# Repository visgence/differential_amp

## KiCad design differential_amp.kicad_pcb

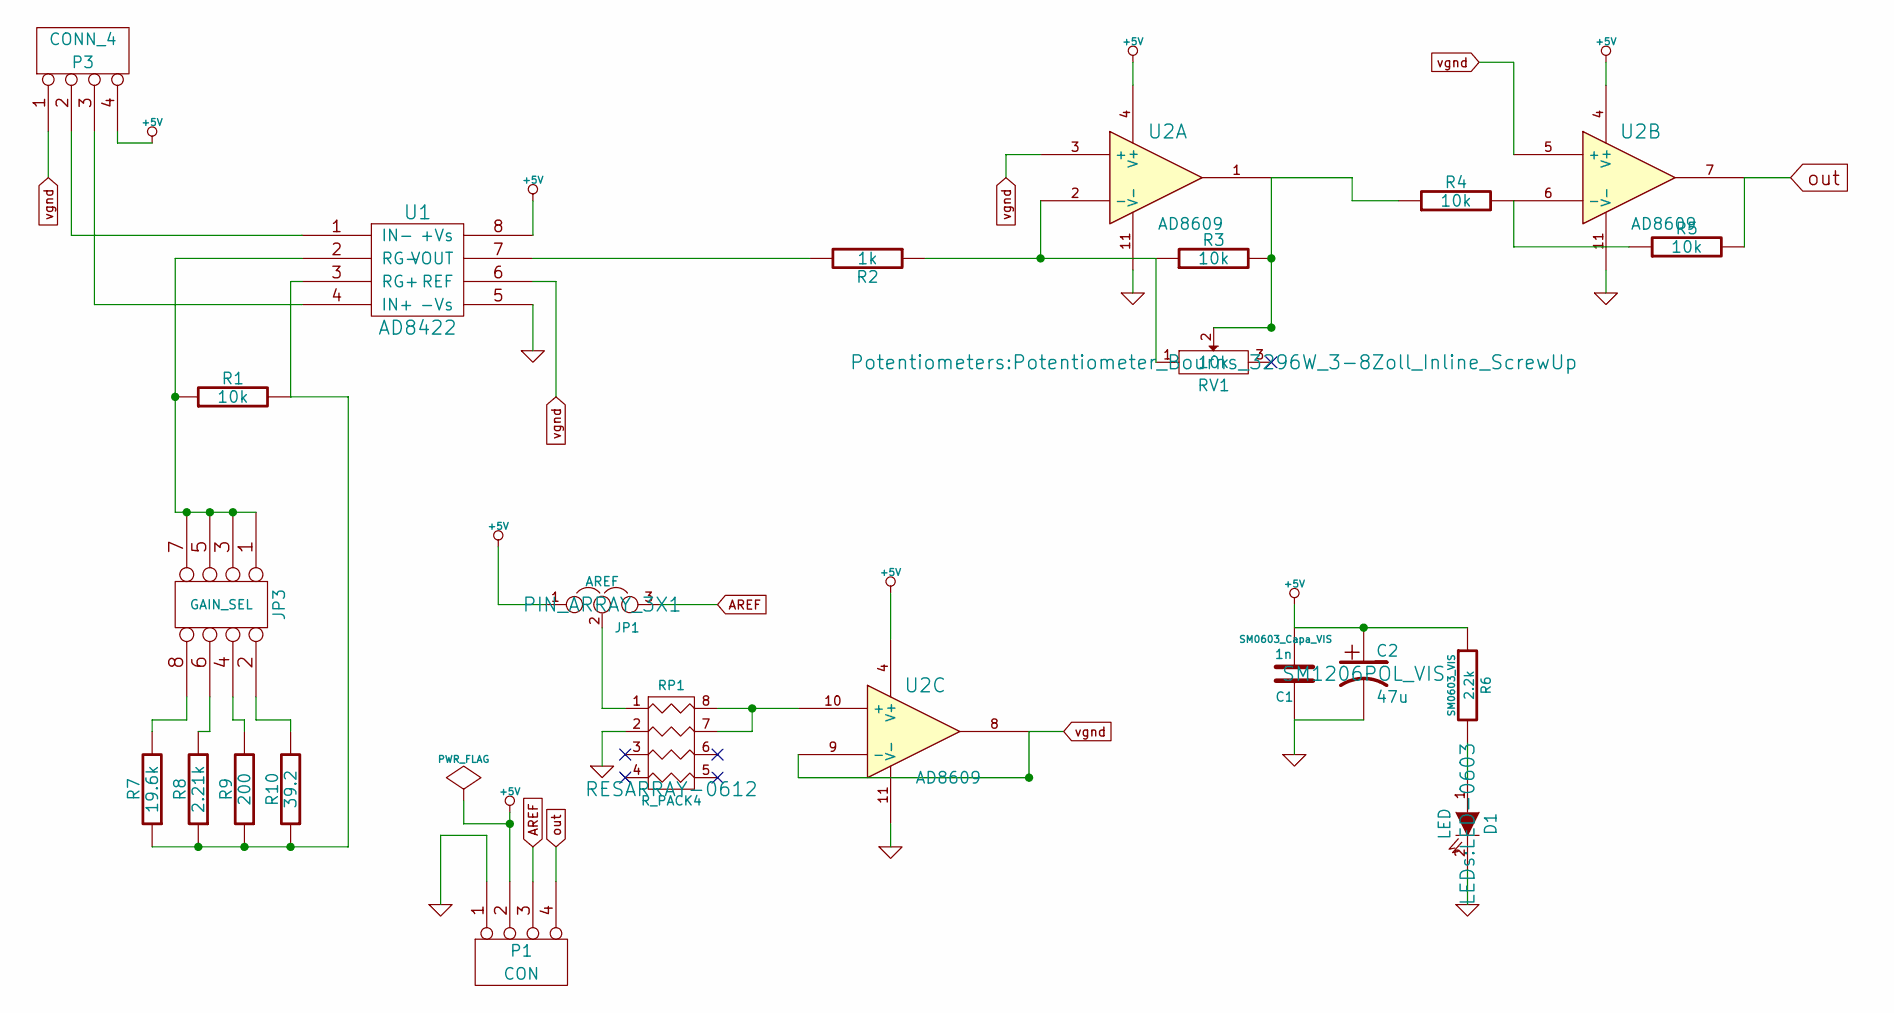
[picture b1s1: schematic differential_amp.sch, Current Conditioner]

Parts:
C1: 1n; SM0603_Capa_VIS
C2: 47u; SM1206POL_VIS
D1: LED; LED-0603
JP1: AREF; PIN_ARRAY_3X1
JP3: GAIN_SEL; pin_array_4x2
P1: CON; bornier4
P3: CONN_4; bornier4
R1, R3, R4, R5: 10k; SM0603_VIS
R2: 1k; SM0603_VIS
R6: 2.2k; SM0603_VIS
R7: 19.6k; SM0603_VIS
R8: 2.21k; SM0603_VIS
R9: 200; SM0603_VIS
R10: 39.2; SM0603_VIS
RP1: R_PACK4; RESARRAY-0612
RV1: 10k; Potentiometer_Bourns_3296W_3-8Zoll_Inline_ScrewUp
U1: AD8422; SO8E
U2: AD8609; SO14E

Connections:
+5V: C1.2, C2.1, JP1.1, P1.2, P3.4, R6.1, U1.8 (+Vs), U2.4 (V+)
AREF: JP1.3, P1.3
GND: C1.1, C2.2, D1.2 (K), P1.1, RP1.2, U1.5 (-Vs), U2.11 (V-)
unnamed: D1.1 (A), R6.2
unnamed: JP1.2, RP1.1
unnamed: JP3.1, JP3.3, JP3.5, JP3.7, R1.1, U1.2 (RG-)
unnamed: JP3.2, R10.2
unnamed: JP3.4, R9.2
unnamed: JP3.6, R8.2
unnamed: JP3.8, R7.2
unnamed: P3.2, U1.1 (IN-)
unnamed: P3.3, U1.4 (IN+)
unnamed: R1.2, R7.1, R8.1, R9.1, R10.1, U1.3 (RG+)
unnamed: R2.1, R3.1, RV1.1, U2.2 (-)
unnamed: R2.2, U1.7 (VOUT)
unnamed: R3.2, R4.1, RV1.2, U2.1
unnamed: R4.2, R5.1, U2.6 (-)
unnamed: RP1.7 (R2), RP1.8 (R1), U2.10 (+)
out: P1.4, R5.2, U2.7
vgnd: P3.1, U1.6 (REF), U2.3 (+), U2.5 (+), U2.8, U2.9 (-)

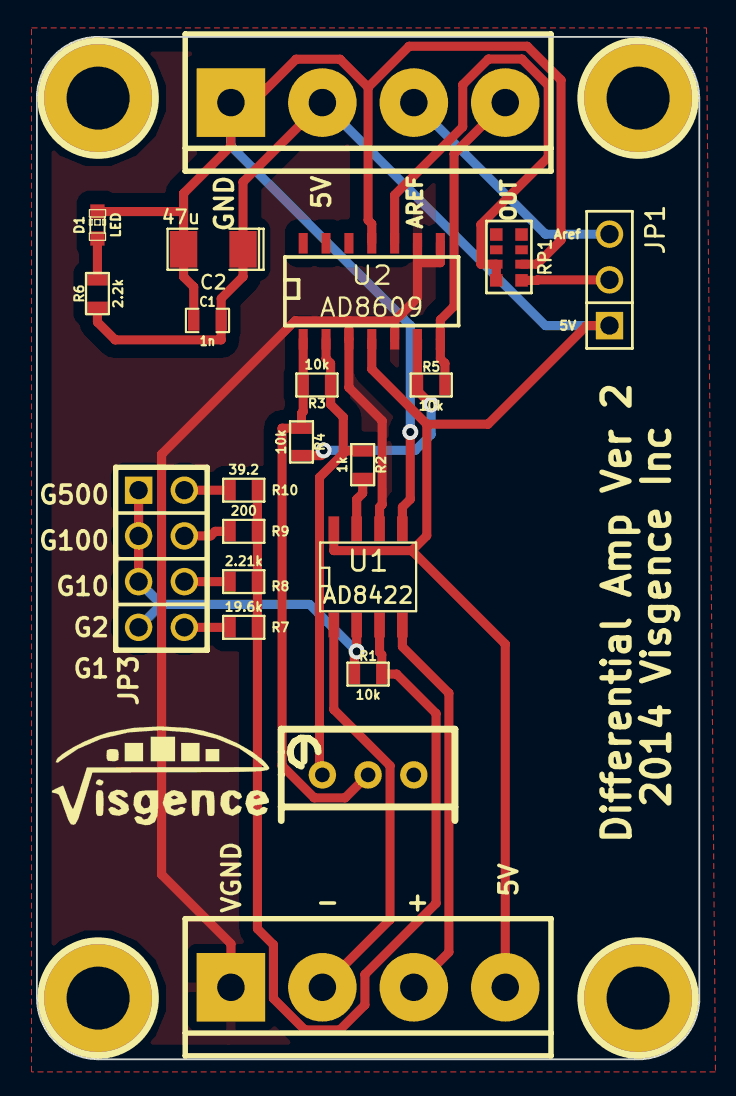
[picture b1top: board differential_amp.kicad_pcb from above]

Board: 2 copper layers, 36.8 x 56.8 mm, 26 parts (0 on the bottom side), 20 nets.

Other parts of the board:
G1: LOGO
h1, h2, h3, h4: pin; 1pin_C

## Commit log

2014-05-19 Started building PCB
2014-05-19 Did PCB layout
2014-05-19 Did some routing
2014-05-23 Routed PCB
2014-05-23 removed x on schematic
2014-05-27 Renamed to differential_amp
2014-05-31 Added gain selection and 5v output on rj45
2014-05-31 resave
2014-08-18 Removed rj45, added multiturn pot
